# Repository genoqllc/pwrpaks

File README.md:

# wh3lk submodular power pack

A lil [eurorack power module](https://kicanvas.org/?github=https%3A%2F%2Fgithub.com%2Fgenoqllc%2Fwh3lk%2Fblob%2Fmain%2Fhardware%2Fwh3lk.kicad_pcb), primilary for prototyping. Takes 16 pin eurorack power and outputs:

- +12V
- +5V
- +3.3V
- +3.3VA (filtered for analog devices)
- -12V
- -10V reference
- GND

## Releases

Upon merging to `main` and creating a release, the [`Makefile.yml` Github Action](https://github.com/genoqllc/wh3lk/actions/workflows/makefile.yml) will build the project and attach the following to the release:

- `wh3lk-$(GIT_TAG).zip` - Gerbers, drill files, DRC report
- `wh3lk-$(GIT_TAG).bom.csv` - A BOM in CSV format, ready for JLCPCB assembly
- `wh3lk-$(GIT_TAG).bom.xml` - Original KiCad XML BOM
- `wh3lk-$(GIT_TAG).pos.csv` - A POS in CSV format, ready for JLCPCB assembly

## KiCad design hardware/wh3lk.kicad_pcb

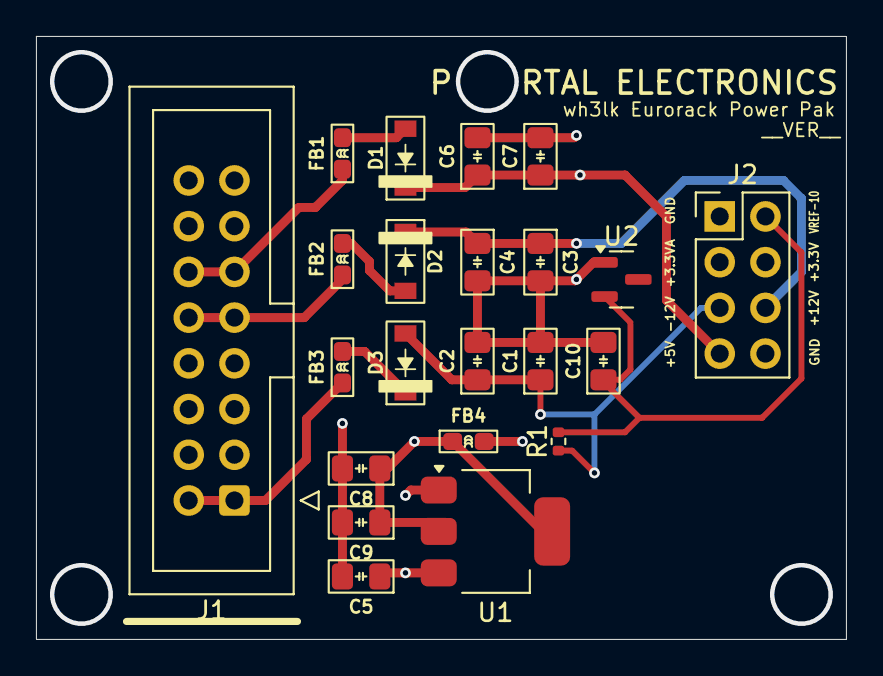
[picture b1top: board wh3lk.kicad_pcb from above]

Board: 4 copper layers, 45.0 x 33.5 mm, 22 parts (0 on the bottom side), 13 nets.

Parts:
C1, C2, C3, C4, C5, C6, C7, C10: 22uF; C_0805_HandSolder
C8: 10uF; C_0805_HandSolder
C9: 100nF; C_0805_HandSolder
D1, D2, D3: 30V; D_SOD-123
FB1, FB2, FB3, FB4: 600R@100MHz; L_0603_HandSolder
J1: Eurorack_Power; IDC-Header_2x08_P2.54mm_Vertical
J2: Conn_01x08_Pin; PinHeader_2x04_P2.54mm_Vertical
R1: 2k2R; R_0402_1005Metric
U1: LD1117S33TR_SOT223; SOT-223-3_TabPin2
U2: LM4040DBZ-10; SOT-23

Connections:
+3.3V: C8.1, C9.1, FB4.1, J2.4, U1.2 (VO)
+3.3VA: FB4.2, J2.3
+5V: C5.1, C6.1, C7.1, D1.1 (K), J2.7, U1.3 (VI)
+12V: C3.1, C4.1, D2.1 (K), J2.6
-12V: C1.1, C2.1, D3.2 (A), J2.5, R1.1
GND: C1.2, C2.2, C3.2, C4.2, C5.2, C6.2, C7.2, C8.2, C9.2, C10.2, J1.3 (GND), J1.4 (GND), J1.5 (GND), J1.6 (GND), J1.7 (GND), J1.8 (GND), J2.1, J2.8, U1.1 (GND), U2.1 (K)
unnamed: D1.2 (A), FB1.2
unnamed: D2.2 (A), FB2.2
unnamed: D3.1 (K), FB3.2
RACK+5V: FB1.1, J1.11 (+5V), J1.12
RACK+12V: FB2.1, J1.9 (+12V), J1.10 (+12V)
RACK-12V: FB3.1, J1.1 (-12V), J1.2 (-12V)
VREF-10: C10.1, J2.2, R1.2, U2.2 (A)

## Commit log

2024-09-08 Establish License
2024-09-08 typos
2024-09-09 initiall schematic and board
2024-09-09 Corrected resistor package, deleted unused files and gerbers
2024-09-09 Moved mounting holes to GND
2024-09-09 bom generation
2024-09-09 Makefile to export to JCLPCB for fab and assembly
2024-09-09 Add pos into build:
2024-09-09 jclpcb wants pos as a csv
2024-09-09 fix 10uF cap part ref
2024-09-09 oops added csv here
2024-09-09 wh3lk: Initial schematic and board (#1)
    * initiall schematic and board
    * Update README.md
    * Corrected resistor package, deleted unused files and gerbers
    * Moved mounting holes to GND
    * bom generation
    * Makefile to export to JCLPCB for fab and assembly
2024-09-09 Use the tag, if available, otherwise short hash
2024-09-09 Use the tag, if available, otherwise short hash (#2)
2024-09-10 Removed ohm symbol to not break JCLPCB BOM
2024-09-10 Removed ohm symbol to not break JCLPCB BOM (#3)
2024-09-10 Basic build workflow, attempt 1
2024-09-10 Readme - added info about release process
2024-09-10 Build: include xsltproc
2024-09-10 Change to run on pho
2024-09-10 Triggering workflow
2024-09-10 Setting to run on self-hosted
2024-09-10 Back to ubuntu
2024-09-10 Readme - added info about release process (#4)
    * Readme - added info about release process
    * Triggering workflow
    * Triggering workflow
    * Triggering workflow
2024-09-10 Adding github token to release action
2024-09-11 README - Added release details
2024-09-11 Link to KiCanvas!
2024-09-12 s/JCLPCB/JLCPCB
2024-09-20 something wip
2024-09-20 Assign board version via git tag on build
2024-09-20 Assign board version via git tag on build (#5)
2024-09-20 Change to voltage ref more available at JLCPCB
2024-09-20 more available, cheaper 10 uF cap
2024-09-20 prepping to make makefile work with multiple sch
2024-09-20 cheaper 100 nF cap
2024-09-20 Generate BOM per sch, then merge
2024-09-20 remove unused VERSIONED_SCHEMATIC
2024-09-20 hide some boring ops
2024-09-20 o ya install rename
2024-09-20 More available, cheaper parts & fix BOM (#6)
    * Change to voltage ref more available at JLCPCB
    * more available, cheaper 10 uF cap
    * prepping to make makefile work with multiple sch
    * cheaper 100 nF cap
    * Generate BOM per sch, then merge
    * remove unused VERSIONED_SCHEMATIC
2024-09-21 Changed 2.2kR resistor to something more available
2024-09-21 Changed 2.2kR resistor to something more available (#7)
2024-09-28 Flipped -12V rail b/c I had it wrong
2024-09-28 ok, REALLY fixed the -12v diode
